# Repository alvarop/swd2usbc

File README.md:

# SWD2USBC Project

Have you ever wanted to debug your device over USB-C? Sometimes there's not enough room for a JTAG/SWD connector, or even [Tag-Connect](https://www.tag-connect.com/) pads!

For history and all of the details, check out [my detailed write up here](https://alvarop.com/2025/03/swd-to-usbc/).

## SWD2USBC

Full featured adapter with Debug Accessory Mode support. Includes an ATTiny microcontroller to set the correct pull-up resistors on CC1/CC2 to provide accurate charge current to the target. Has a USB-C plug so no extra USB-C cable required

### SWD2USBC Firmware
The ATTiny firmware doesn't do much. It reads the voltage on the CC1/CC2 line that is pulled up and determines the available charge current. It then pulls up CC1 **and** CC2 to provide the charge current to the device under Debug Accessory Mode.

## SWD2USBC Basic
 
Simple adapter with no Debug Accessory Mode. Assumes target SWD lines wired up directly to TX1/2 as listed above. Requires USB3/Thunderbolt C to C cable to connect to target.

## Sample Target 

Example target device. Fully featured with CC1/2 comparators to connect/disconnect SWD lines if Debug Accessory Mode is active. Target is an RP2040 instead of STM32 since it's easier to source.

### Sample Target Firmware
The sample target firmware does basic USB charge detection using the CC lines. When the Debug Accessory Mode is enabled, both CC1/CC2 are used, otherwise, the single CC line is used. There's an LED (D3) which lights up when Debug Accessory Mode is enabled.

The charge current is printed out over UART, but it is also displayed using the two LEDs. The blink patterns are:
* **500mA** - LED1 (D1) blinks 
* **1500mA** - LED2 (D2) blinks 
* **3000mA** - Both LED1 (D1) and LED2 (D2) blink at the same time
* **Other/Error** - Both LED1 (D1) and LED2 (D2) alternating blink

## Sample Target Basic

Basic example target. Similar to the sample target above, but does not include any comparators/switches. SWD lines are directly connected to the USB-C connector.

## SWD2USBC Programmer
Simple adapter PCB to connect the AVRISP V2 connector to USB-C to program the ATTiny in the SWD2USBC device.

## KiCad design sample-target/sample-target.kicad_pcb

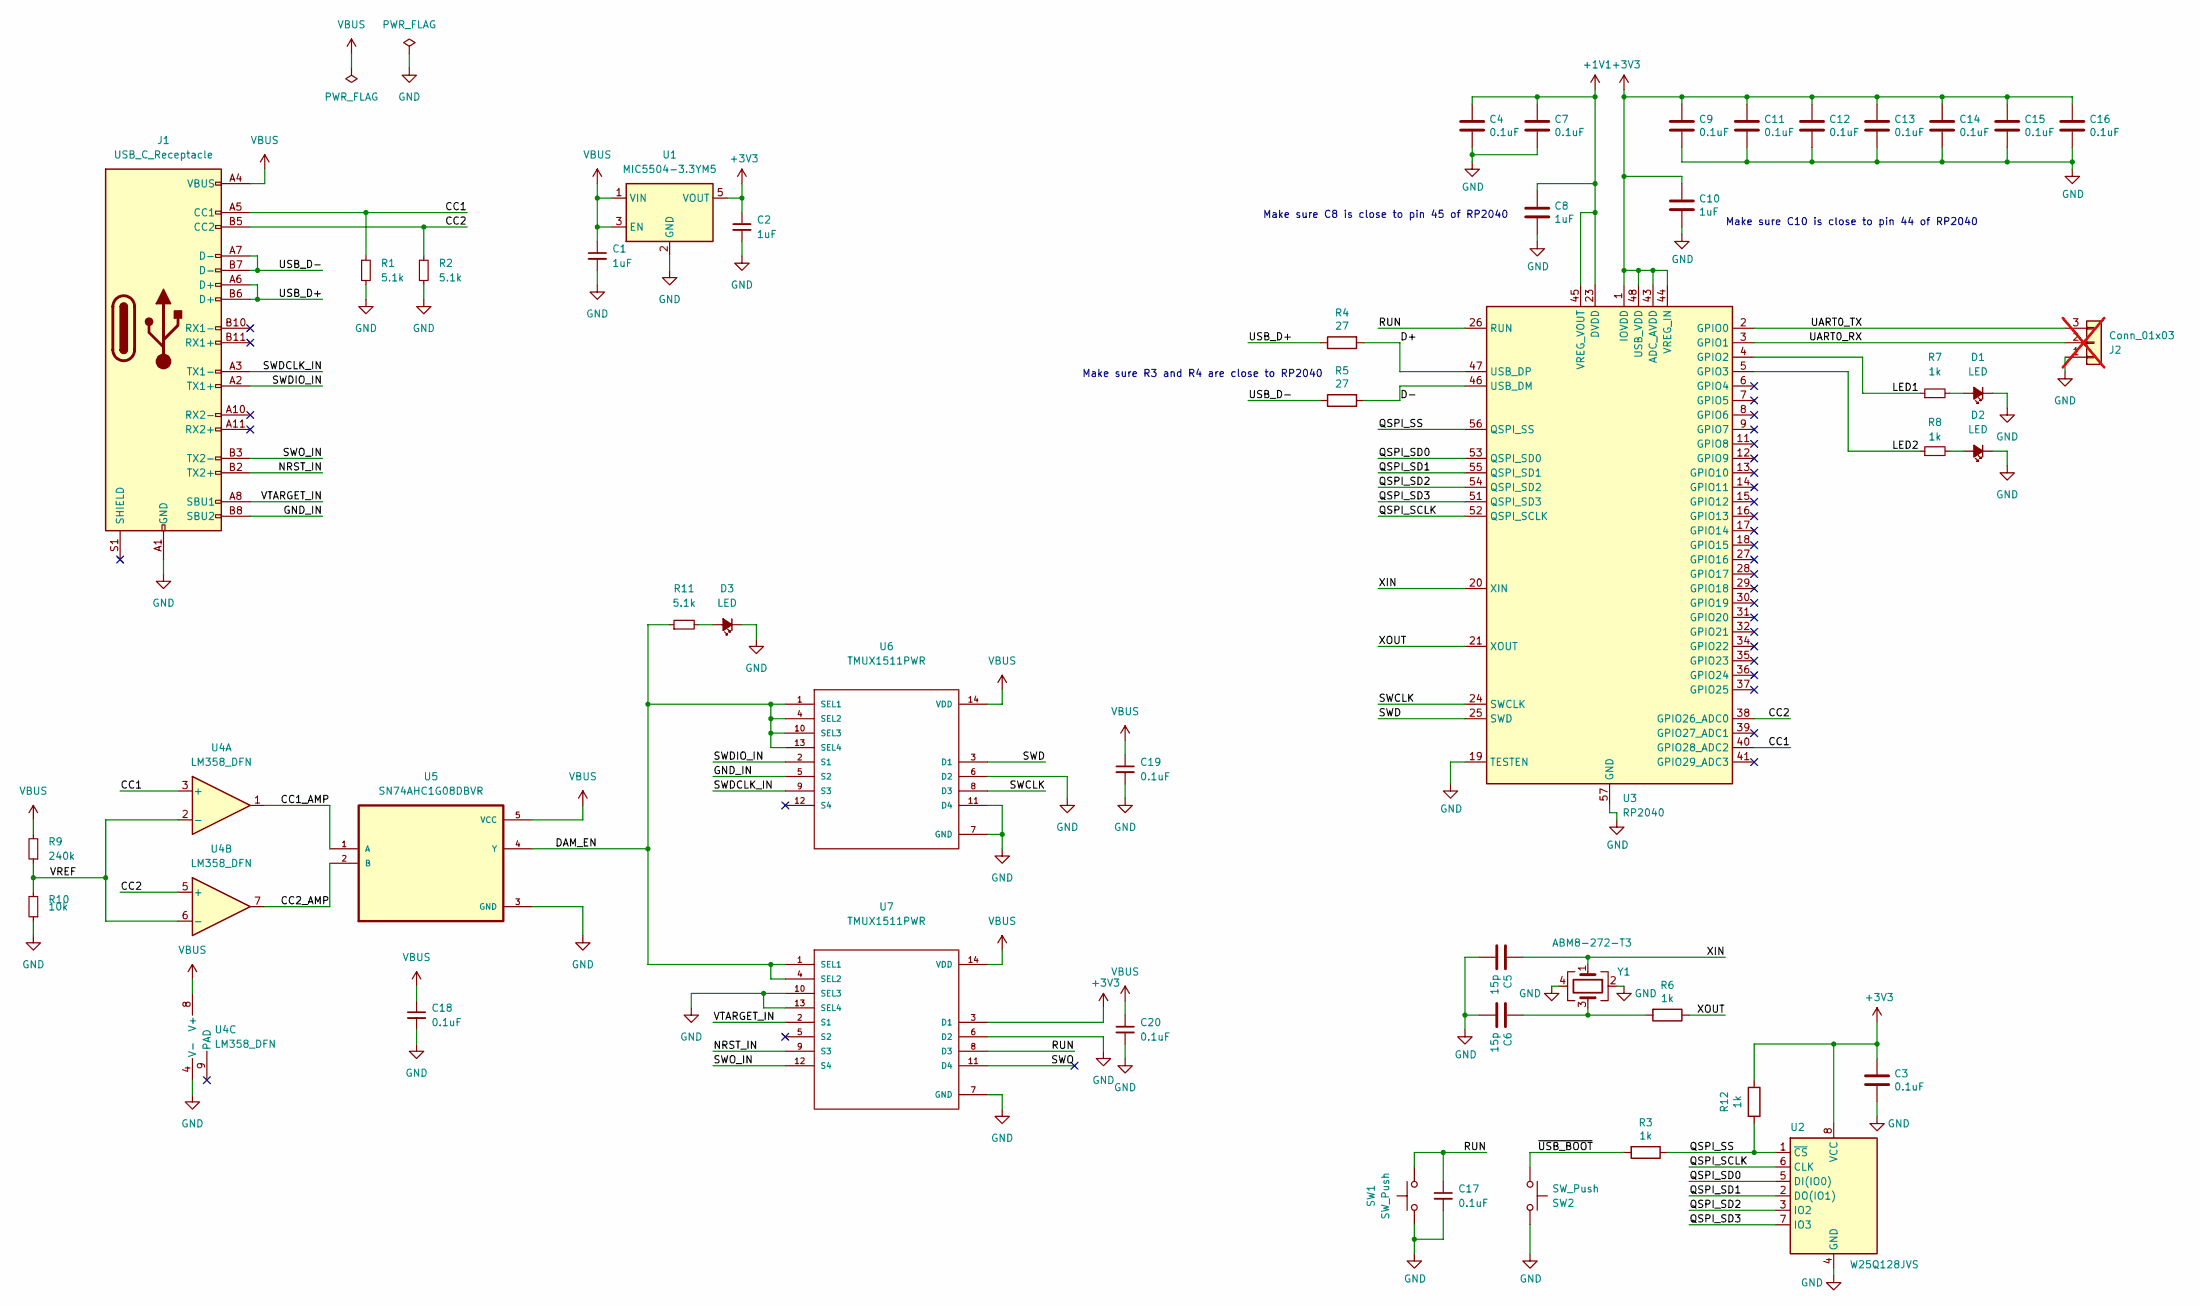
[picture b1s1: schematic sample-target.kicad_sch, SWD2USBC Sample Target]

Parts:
C1, C2, C8, C10: 1uF; C_0402_1005Metric; LCSC C52923
C3, C4, C7, C9, C11, C12, C13, C14, C15, C16, C17, C18, C19, C20: 0.1uF; C_0402_1005Metric; MPN CL05B104KB54PNC; LCSC C307331
C5, C6: 15p; C_0402_1005Metric; LCSC C106997
D1, D2, D3: LED; LED_0603_1608Metric; LCSC C72038
J1: USB_C_Receptacle; UT11113-11602-7H; MPN UT11113-11602-7H; LCSC C2761408
J2: Conn_01x03; PinHeader_1x03_P2.54mm_Vertical; not fitted
R1, R2, R11: 5.1k; R_0402_1005Metric; LCSC C105872
R3, R6, R7, R8, R12: 1k; R_0402_1005Metric; LCSC C4190
R4, R5: 27; R_0402_1005Metric; LCSC C137890
R9: 240k; R_0402_1005Metric; LCSC C138029
R10: 10k; R_0402_1005Metric; LCSC C25744
SW1, SW2: SW_Push; SW-SMD_L3.9-W3.0-P4.45; MPN SKRKAEE020; LCSC C115357
U1: MIC5504-3.3YM5; SOT-23-5; MPN MIC5504-3.3YM5-TR; LCSC C41348078
U2: W25Q128JVS; SOIC-8_5.23x5.23mm_P1.27mm; MPN W25Q128JVS; LCSC C97521
U3: RP2040; QFN-56-1EP_7x7mm_P0.4mm_EP3.2x3.2mm; MPN RP2040; LCSC C2040
U4: LM358_DFN; DFN-8-1EP_2x2mm_P0.5mm_EP1.05x1.75mm; MPN LM358QT; LCSC C2649392
U5: SN74AHC1G08DBVR; SOT95P280X145-5N; MPN SN74AHC1G08DBVR; LCSC C7467
U6, U7: TMUX1511PWR; SOP65P640X120-14N; MPN TMUX1511PWR; LCSC C2866750
Y1: ABM8-272-T3; Crystal_SMD_3225-4Pin_3.2x2.5mm; MPN ABM8-272-T3; LCSC C20625731

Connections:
+1V1: C4.1, C7.1, C8.1, U3.23 (DVDD), U3.45 (VREG_VOUT), U3.50 (DVDD)
+3V3: C2.1, C3.1, C9.1, C10.1, C11.1, C12.1, C13.1, C14.1, C15.1, C16.1, R12.1, U1.5 (VOUT), U2.8 (VCC), U3.1 (IOVDD), U3.10 (IOVDD), U3.22 (IOVDD), U3.33 (IOVDD), U3.42 (IOVDD), U3.43 (ADC_AVDD), U3.44 (VREG_IN), U3.48 (USB_VDD), U3.49 (IOVDD), U7.3 (D1)
/CC1: J1.A5 (CC1), R1.1, U3.40 (GPIO28_ADC2), U4.3 (+)
/CC1_AMP: U4.1, U5.1 (A)
/CC2: J1.B5 (CC2), R2.1, U3.38 (GPIO26_ADC0), U4.5 (+)
/CC2_AMP: U4.7, U5.2 (B)
/D+: R4.2, U3.47 (USB_DP)
/D-: R5.2, U3.46 (USB_DM)
/DAM_EN: R11.1, U5.4 (Y), U6.1 (SEL1), U6.4 (SEL2), U6.10 (SEL3), U6.13 (SEL4), U7.1 (SEL1), U7.4 (SEL2)
/GND_IN: J1.B8 (SBU2), U6.5 (S2)
/LED1: R7.1, U3.4 (GPIO2)
/LED2: R8.1, U3.5 (GPIO3)
/NRST_IN: J1.B2 (TX2+), U7.9 (S3)
/QSPI_SCLK: U2.6 (CLK), U3.52 (QSPI_SCLK)
/QSPI_SD0: U2.5 (DI(IO0)), U3.53 (QSPI_SD0)
/QSPI_SD1: U2.2 (DO(IO1)), U3.55 (QSPI_SD1)
/QSPI_SD2: U2.3 (IO2), U3.54 (QSPI_SD2)
/QSPI_SD3: U2.7 (IO3), U3.51 (QSPI_SD3)
/QSPI_SS: R3.1, R12.2, U2.1 (~CS), U3.56 (QSPI_SS)
/RUN: C17.1, SW1.2, U3.26 (RUN), U7.8 (D3)
/SWCLK: U3.24 (SWCLK), U6.8 (D3)
/SWD: U3.25 (SWD), U6.3 (D1)
/SWDCLK_IN: J1.A3 (TX1-), U6.9 (S3)
/SWDIO_IN: J1.A2 (TX1+), U6.2 (S1)
/SWO: U7.11 (D4)
/SWO_IN: J1.B3 (TX2-), U7.12 (S4)
/UART0_RX: J2.2, U3.3 (GPIO1)
/UART0_TX: J2.3, U3.2 (GPIO0)
/USB_D+: J1.A6 (D+), J1.B6 (D+), R4.1
/USB_D-: J1.A7 (D-), J1.B7 (D-), R5.1
/VREF: R9.1, R10.2, U4.2 (-), U4.6 (-)
/VTARGET_IN: J1.A8 (SBU1), U7.2 (S1)
/XIN: C5.1, U3.20 (XIN), Y1.1
/XOUT: R6.1, U3.21 (XOUT)
/~USB_BOOT: R3.2, SW2.2
GND: C1.2, C2.2, C3.2, C4.2, C5.2, C6.2, C7.2, C8.2, C9.2, C10.2, C11.2, C12.2, C13.2, C14.2, C15.2, C16.2, C17.2, C18.2, C19.2, C20.2, D1.1 (K), D2.1 (K), D3.1 (K), J1.A1 (GND), J1.A12 (GND), J1.B1 (GND), J1.B12 (GND), J2.1, R1.2, R2.2, R10.1, SW1.1, SW2.1, U1.2 (GND), U2.4 (GND), U3.19 (TESTEN), U3.57 (GND), U4.4 (V-), U5.3 (GND), U6.6 (D2), U6.7 (GND), U6.11 (D4), U7.6 (D2), U7.7 (GND), U7.10 (SEL3), U7.13 (SEL4), Y1.2, Y1.4
unnamed: C6.1, R6.2, Y1.3
unnamed: D1.2 (A), R7.2
unnamed: D2.2 (A), R8.2
unnamed: D3.2 (A), R11.2
VBUS: C1.1, C18.1, C19.1, C20.1, J1.A4 (VBUS), J1.A9 (VBUS), J1.B4 (VBUS), J1.B9 (VBUS), R9.2, U1.1 (VIN), U1.3 (EN), U4.8 (V+), U5.5 (VCC), U6.14 (VDD), U7.14 (VDD)

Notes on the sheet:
Make sure C10 is close to pin 44 of RP2040
Make sure C8 is close to pin 45 of RP2040
Make sure R3 and R4 are close to RP2040

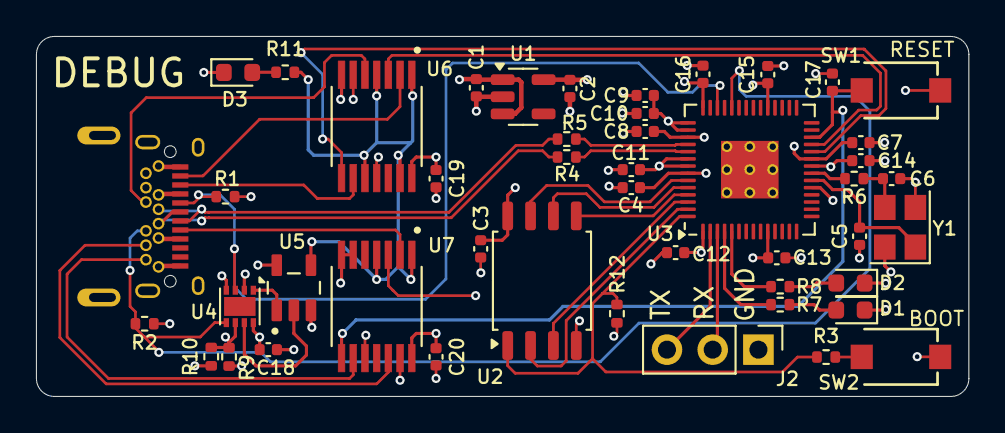
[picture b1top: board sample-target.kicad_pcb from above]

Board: 4 copper layers, 51.8 x 20.0 mm, 47 parts (0 on the bottom side), 40 nets.

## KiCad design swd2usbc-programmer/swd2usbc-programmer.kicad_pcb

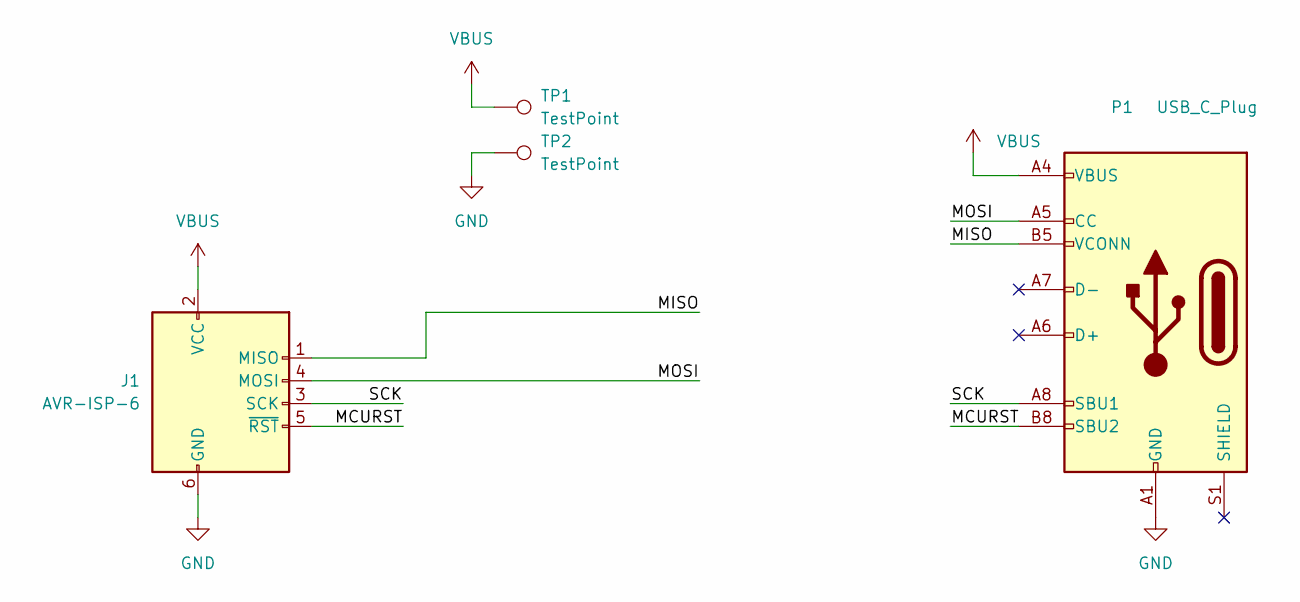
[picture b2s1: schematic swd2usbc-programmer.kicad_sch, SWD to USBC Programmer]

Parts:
J1: AVR-ISP-6; IDC-Header_2x03_P2.54mm_Vertical; MPN 30306-6002HB
P1: USB_C_Plug; TYPE-C-31-G-06; MPN TYPE-C-31-G-06
TP1, TP2: TestPoint; TestPoint_Pad_D2.5mm

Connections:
/MCURST: J1.5 (~RST), P1.B8 (SBU2)
/MISO: J1.1 (MISO), P1.B5 (VCONN)
/MOSI: J1.4 (MOSI), P1.A5 (CC)
/SCK: J1.3 (SCK), P1.A8 (SBU1)
GND: J1.6 (GND), P1.A1 (GND), P1.A12 (GND), P1.B1 (GND), P1.B12 (GND), TP2.1
VBUS: J1.2 (VCC), P1.A4 (VBUS), P1.A9 (VBUS), P1.B4 (VBUS), P1.B9 (VBUS), TP1.1

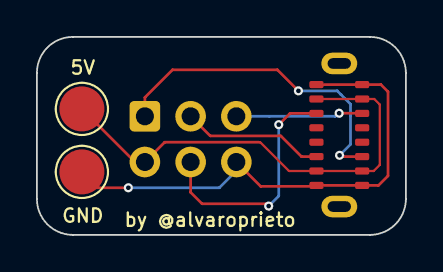
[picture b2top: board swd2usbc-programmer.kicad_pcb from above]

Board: 2 copper layers, 20.5 x 11.0 mm, 4 parts (1 on the bottom side), 6 nets.

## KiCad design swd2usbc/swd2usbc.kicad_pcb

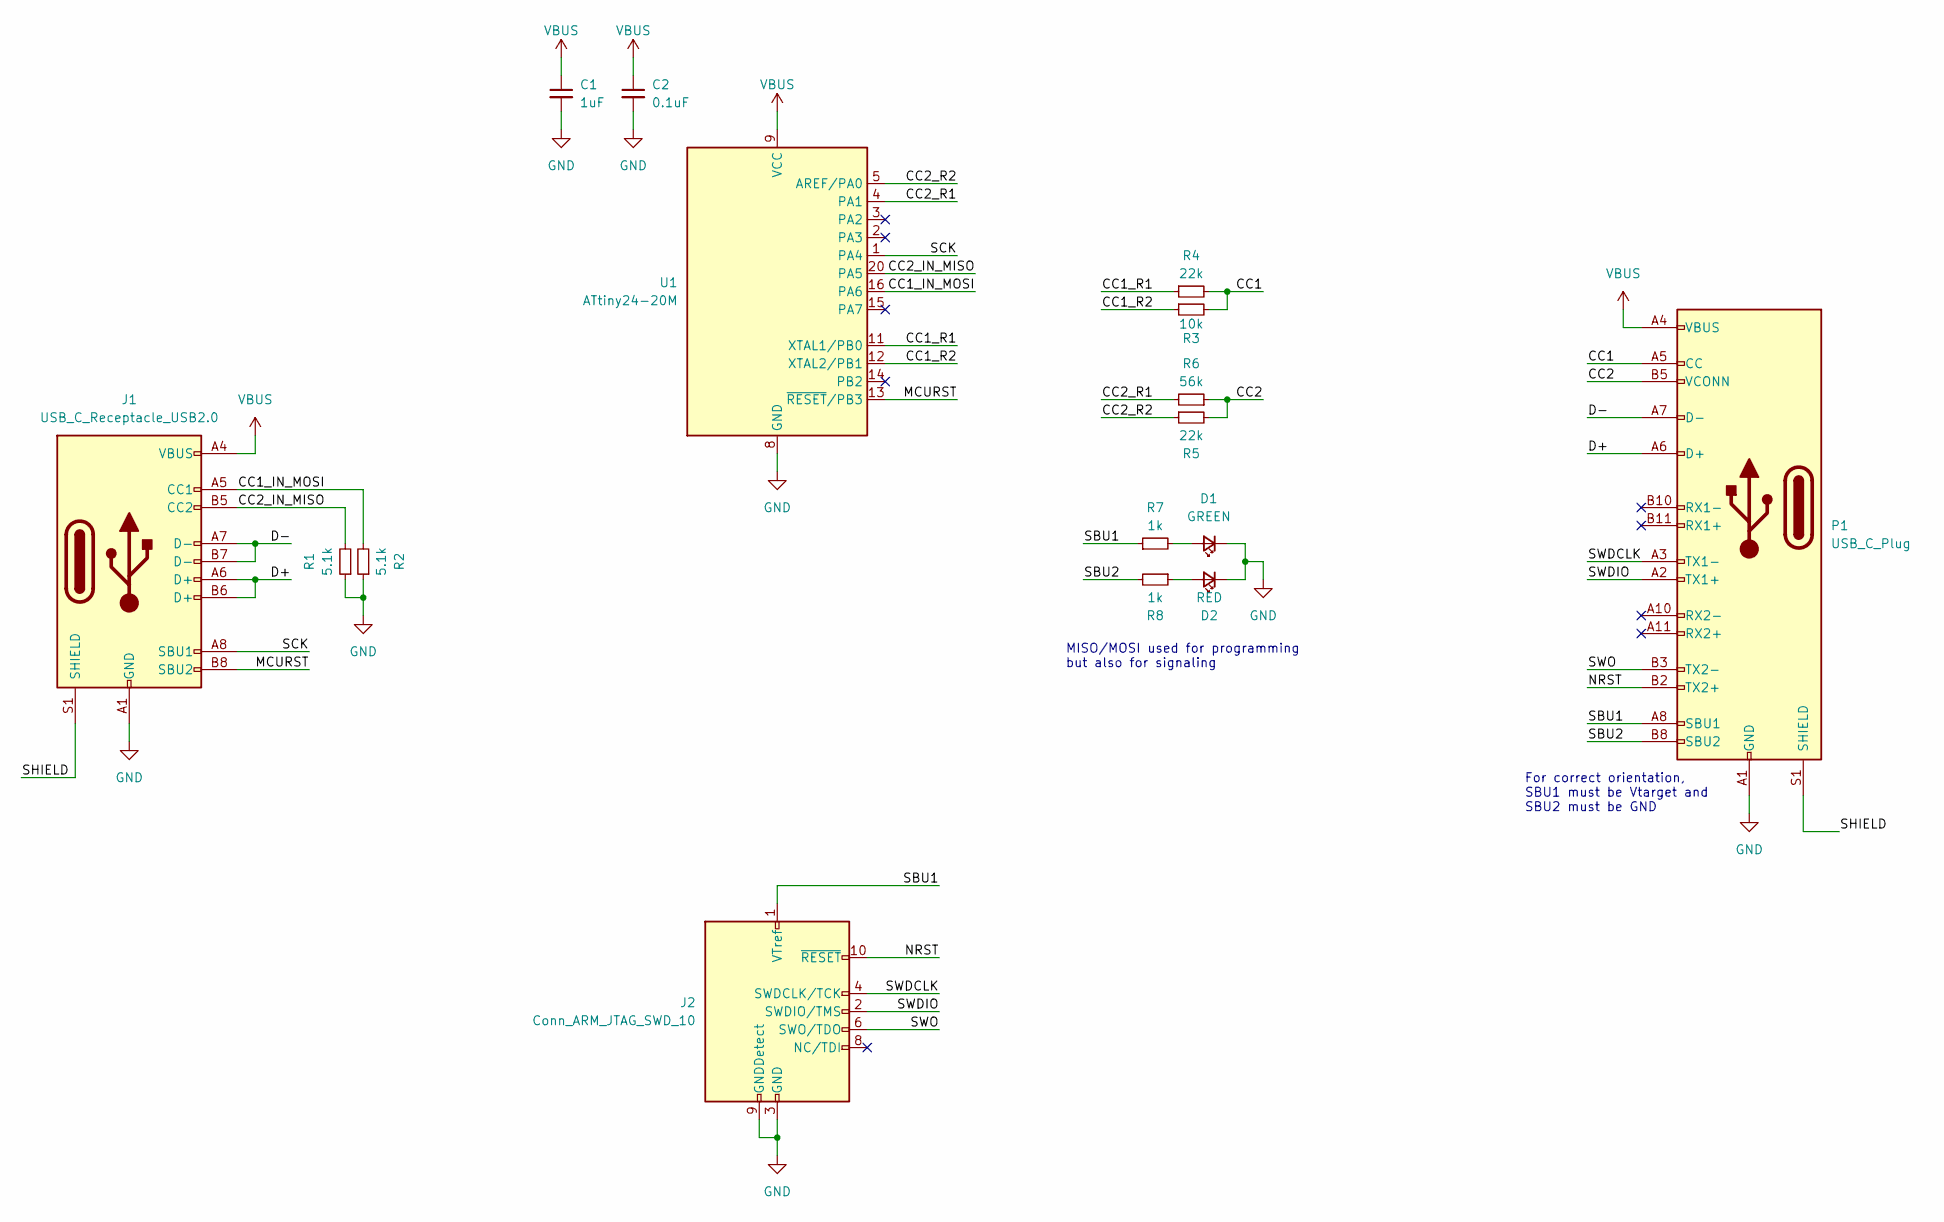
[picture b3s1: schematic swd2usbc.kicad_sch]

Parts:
C1: 1uF; C_0402_1005Metric; MPN CL05A105KO5NNNC; LCSC C52923
C2: 0.1uF; C_0402_1005Metric; MPN CL05B104KO5NNNC; LCSC C307331
D1: GREEN; LED_0603_1608Metric; MPN SML-D12M8WT86; LCSC C965804
D2: RED; LED_0603_1608Metric; MPN SML-D12U1WT86; LCSC C2286
J1: USB_C_Receptacle_USB2.0; USB4105-GF-A; MPN USB4105-GF-A; LCSC C136423
J2: Conn_ARM_JTAG_SWD_10; SAMTEC_FTSH-105-01-F-DV-P-TR; MPN FTSH-105-01-F-DV-K; LCSC C2935458
P1: USB_C_Plug; MOLEX_1054440011; MPN 1054440011; LCSC C561769
R1, R2: 5.1k; R_0402_1005Metric; MPN RC0402FR-075K1L; LCSC C105872
R3: 10k; R_0402_1005Metric; MPN RC0402FR-0710KL; LCSC C25744
R4, R5: 22k; R_0402_1005Metric; MPN RC0402FR-0722KL; LCSC C25768
R6: 56k; R_0402_1005Metric; MPN RC0402FR-0756KL; LCSC C25796
R7, R8: 1k; R_0402_1005Metric; MPN RC0402FR-071KL; LCSC C4190
U1: ATtiny24-20M; ATTINY24A-MMH; MPN ATTINY24A-MMH; LCSC C617902

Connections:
/CC1: P1.A5 (CC), R3.2, R4.2
/CC1_IN_MOSI: J1.A5 (CC1), R2.2, U1.16 (PA6)
/CC1_R1: R4.1, U1.11 (XTAL1/PB0)
/CC1_R2: R3.1, U1.12 (XTAL2/PB1)
/CC2: P1.B5 (VCONN), R5.2, R6.1
/CC2_IN_MISO: J1.B5 (CC2), R1.2, U1.20 (PA5)
/CC2_R1: R6.2, U1.4 (PA1)
/CC2_R2: R5.1, U1.5 (AREF/PA0)
/D+: J1.A6 (D+), J1.B6 (D+), P1.A6 (D+)
/D-: J1.A7 (D-), J1.B7 (D-), P1.A7 (D-)
/MCURST: J1.B8 (SBU2), U1.13 (~RESET/PB3)
/NRST: J2.10 (~RESET), P1.B2 (TX2+)
/SBU1: J2.1 (VTref), P1.A8 (SBU1), R7.1
/SBU2: P1.B8 (SBU2), R8.2
/SCK: J1.A8 (SBU1), U1.1 (PA4)
/SHIELD: J1.S1 (SHIELD), P1.S1 (SHIELD)
/SWDCLK: J2.4 (SWDCLK/TCK), P1.A3 (TX1-)
/SWDIO: J2.2 (SWDIO/TMS), P1.A2 (TX1+)
/SWO: J2.6 (SWO/TDO), P1.B3 (TX2-)
GND: C1.2, C2.2, D1.1 (K), D2.1 (K), J1.A1 (GND), J1.A12 (GND), J1.B1 (GND), J1.B12 (GND), J2.3 (GND), J2.5 (GND), J2.9 (GNDDetect), P1.A1 (GND), P1.A12 (GND), P1.B1 (GND), P1.B12 (GND), R1.1, R2.1, U1.8 (GND), U1.21 (GND)
unnamed: D1.2 (A), R7.2
unnamed: D2.2 (A), R8.1
VBUS: C1.1, C2.1, J1.A4 (VBUS), J1.A9 (VBUS), J1.B4 (VBUS), J1.B9 (VBUS), P1.A4 (VBUS), P1.A9 (VBUS), P1.B4 (VBUS), P1.B9 (VBUS), U1.9 (VCC)

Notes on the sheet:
MISO/MOSI used for programming but also for signaling
For correct orientation, SBU1 must be Vtarget and SBU2 must be GND

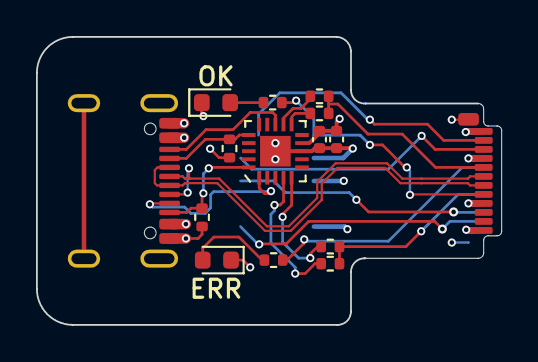
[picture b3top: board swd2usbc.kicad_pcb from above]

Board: 4 copper layers, 25.8 x 16.0 mm, 16 parts (1 on the bottom side), 23 nets.

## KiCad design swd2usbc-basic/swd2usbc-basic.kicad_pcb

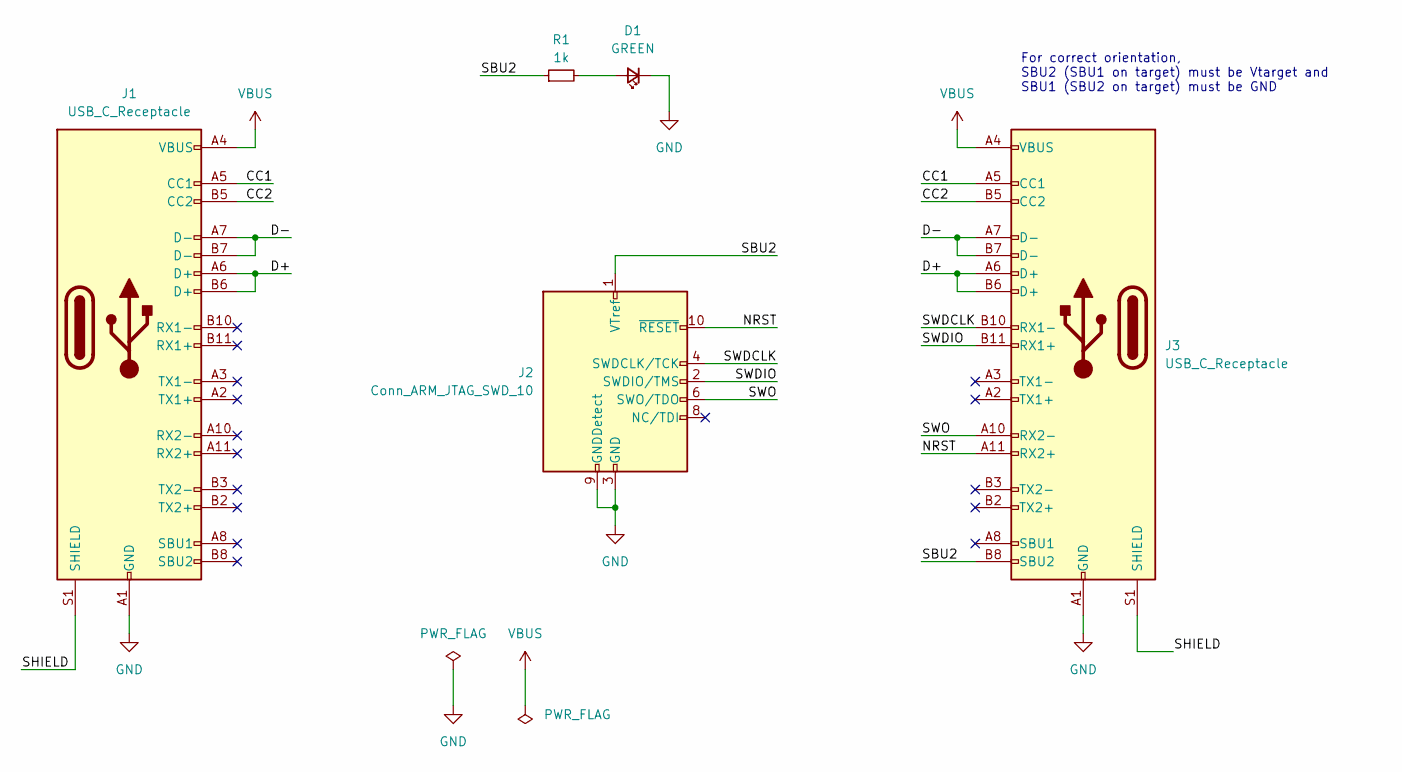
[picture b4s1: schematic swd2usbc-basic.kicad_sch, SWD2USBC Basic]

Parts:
D1: GREEN; LED_0603_1608Metric; MPN SML-D12M8WT86; LCSC C965804
J1, J3: USB_C_Receptacle; MOLEX-1054500101; MPN 1054500101; LCSC C134092
J2: Conn_ARM_JTAG_SWD_10; SAMTEC_FTSH-105-01-F-DV-P-TR; MPN FTSH-105-01-F-DV-K-P-TR; LCSC C19191729
R1: 1k; R_0402_1005Metric; MPN RC0402FR-071KL; LCSC C25744

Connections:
/CC1: J1.A5 (CC1), J3.A5 (CC1)
/CC2: J1.B5 (CC2), J3.B5 (CC2)
/D+: J1.A6 (D+), J1.B6 (D+), J3.A6 (D+), J3.B6 (D+)
/D-: J1.A7 (D-), J1.B7 (D-), J3.A7 (D-), J3.B7 (D-)
/NRST: J2.10 (~RESET), J3.A11 (RX2+)
/SBU2: J2.1 (VTref), J3.B8 (SBU2), R1.1
/SHIELD: J1.S1 (SHIELD), J3.S1 (SHIELD)
/SWDCLK: J2.4 (SWDCLK/TCK), J3.B10 (RX1-)
/SWDIO: J2.2 (SWDIO/TMS), J3.B11 (RX1+)
/SWO: J2.6 (SWO/TDO), J3.A10 (RX2-)
GND: D1.1 (K), J1.A1 (GND), J1.A12 (GND), J1.B1 (GND), J1.B12 (GND), J2.3 (GND), J2.5 (GND), J2.9 (GNDDetect), J3.A1 (GND), J3.A12 (GND), J3.B1 (GND), J3.B12 (GND)
unnamed: D1.2 (A), R1.2
VBUS: J1.A4 (VBUS), J1.A9 (VBUS), J1.B4 (VBUS), J1.B9 (VBUS), J3.A4 (VBUS), J3.A9 (VBUS), J3.B4 (VBUS), J3.B9 (VBUS)

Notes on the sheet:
For correct orientation, SBU2 (SBU1 on target) must be Vtarget and SBU1 (SBU2 on target) must be GND

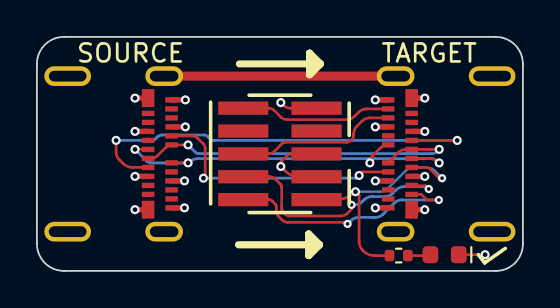
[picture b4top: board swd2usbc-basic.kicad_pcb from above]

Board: 4 copper layers, 27.0 x 13.0 mm, 5 parts (0 on the bottom side), 13 nets.

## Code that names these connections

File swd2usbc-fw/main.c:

#include <avr/io.h>
#include <util/delay.h>

#define MAX(X, Y) ((X) > (Y) ? (X) : (Y))

// Input CC1/CC2
#define CC1 PA6
#define CC2 PA5

// Output CC1/CC2 Rpu's
#define CC1_R2 PB1  // 10 kOhm
#define CC1_R1 PB0  // 22 kOhm
#define CC2_R2 PA0  // 22 kOhm
#define CC2_R1 PA1  // 56 kOhm

typedef enum {
  USB_500MA,
  USB_1500MA,
  USB_3000MA,
} USBCurrent_t;

// Current | CC1/CC2 In | CC1 Rpu          | CC2 Rpu
// 500mA   |    0.42V   | 10 kOhm (CC1_R2) | 22 kOhm (CC2_R2)
// 1.5A    |    0.94V   | 22 kOhm (CC1_R1) | 56 kOhm (CC2_R1)
// 3.0A    |    1.69V   | 10 kOhm (CC1_R2) | 56 kOhm (CC2_R1)

void set_usb_current(USBCurrent_t current) {
  switch (current) {
    case USB_500MA: {
      DDRB &= ~_BV(CC1_R1);
      DDRB |= _BV(CC1_R2);
      PORTB &= ~_BV(CC1_R1);
      PORTB |= _BV(CC1_R2);

      DDRA &= ~_BV(CC2_R1);
      DDRA |= _BV(CC2_R2);
      PORTA &= ~_BV(CC2_R1);
      PORTA |= _BV(CC2_R2);
      break;
    }
    case USB_1500MA: {
      DDRB &= ~_BV(CC1_R2);
      DDRB |= _BV(CC1_R1);
      PORTB &= ~_BV(CC1_R2);
      PORTB |= _BV(CC1_R1);

      DDRA &= ~_BV(CC2_R2);
      DDRA |= _BV(CC2_R1);
      PORTA &= ~_BV(CC2_R2);
      PORTA |= _BV(CC2_R1);
      break;
    }
    case USB_3000MA: {
      DDRB &= ~_BV(CC1_R1);
      DDRB |= _BV(CC1_R2);
      PORTB &= ~_BV(CC1_R1);
      PORTB |= _BV(CC1_R2);

      DDRA &= ~_BV(CC2_R2);
      DDRA |= _BV(CC2_R1);
      PORTA &= ~_BV(CC2_R2);
      PORTA |= _BV(CC2_R1);
      break;
    }
  }
}

uint16_t adc_sample_mv(uint8_t channel) {
  ADMUX = channel;
  ADCSRA |= (1 << ADSC);  // Start conversion

  // Wait for conversion to complete
  while (ADCSRA & (1 << ADSC));

  uint16_t raw_adc_val = ADC;
  uint32_t adc_mv = ((uint32_t)raw_adc_val * 5000) / 1024;

  return adc_mv;
}

// CC1/CC2 voltages for various USB C currents
#define USB_CC_MV_500MA 200
#define USB_CC_MV_1500MA 660
#define USB_CC_MV_3000MA 1230

USBCurrent_t get_cc_current(void) {
  // Read CC1/CC2 values for input current detection
  uint16_t cc1 = adc_sample_mv(CC1);
  uint16_t cc2 = adc_sample_mv(CC2);

  cc1 = MAX(cc1, cc2);

  USBCurrent_t curent;
  if (cc1 <= USB_CC_MV_1500MA) {
    curent = USB_500MA;
  } else if (cc1 <= USB_CC_MV_3000MA) {
    curent = USB_1500MA;
  } else {
    curent = USB_3000MA;
  }

  return curent;
}

int main(void) {
  // Set port B output 0 as inputs
  DDRA &= ~(_BV(CC2_R2) | _BV(CC2_R1));
  DDRB &= ~(_BV(CC1_R2) | _BV(CC1_R1));

  // Set outputs high (so they are on when switched to outputs)
  PORTA = _BV(CC2_R2) | _BV(CC2_R1);
  PORTB = _BV(CC1_R2) | _BV(CC1_R1);

  // ADC Enable with / 16 prescaler (62.5kHz)
  ADCSRA = (1 << ADEN) | 3;

  // Disable digital inputs on ADC pins
  DIDR0 |= _BV(CC1) | _BV(CC2);

  // Default to 500mA charge current to start
  set_usb_current(USB_500MA);

  while (1) {
    set_usb_current(get_cc_current());
    _delay_ms(10);
  }
  return 0;
}

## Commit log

2024-12-31 Initial commit of v4.1 basic
2025-01-05 Add sample targets
2025-01-05 Adding swd2usbc and renaming swd2usbc-basic
2025-01-05 Various fixes while ordering from JLCPCB
2025-01-18 Should have checked my footprints...
    USB-C plug footprint was incorrect. I had fixed it in the library but forgot to update it in the project.........
2025-01-18 Fixed some silkscreen and added OSWH logo
2025-02-15 Add programmer PCB
2025-02-15 Add SWD2USB-C firmware
2025-02-16 Add CC lines to sample targets
2025-02-16 Add sample target firmware
2025-02-17 Add readme with pictures
2025-02-17 Create LICENSE
2025-02-19 Add pull up resistor to spi flash
2025-03-05 Add link to blog post
2025-03-16 Update the incorrect image link (not png but jpg)

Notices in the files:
parts and their libraries:
Copyright 2021 Accelerated Designs. All rights reserved.
